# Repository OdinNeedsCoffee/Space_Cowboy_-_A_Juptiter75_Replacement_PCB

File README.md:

# Space_Cowboy_-_A_Juptiter75_Replacement_PCB

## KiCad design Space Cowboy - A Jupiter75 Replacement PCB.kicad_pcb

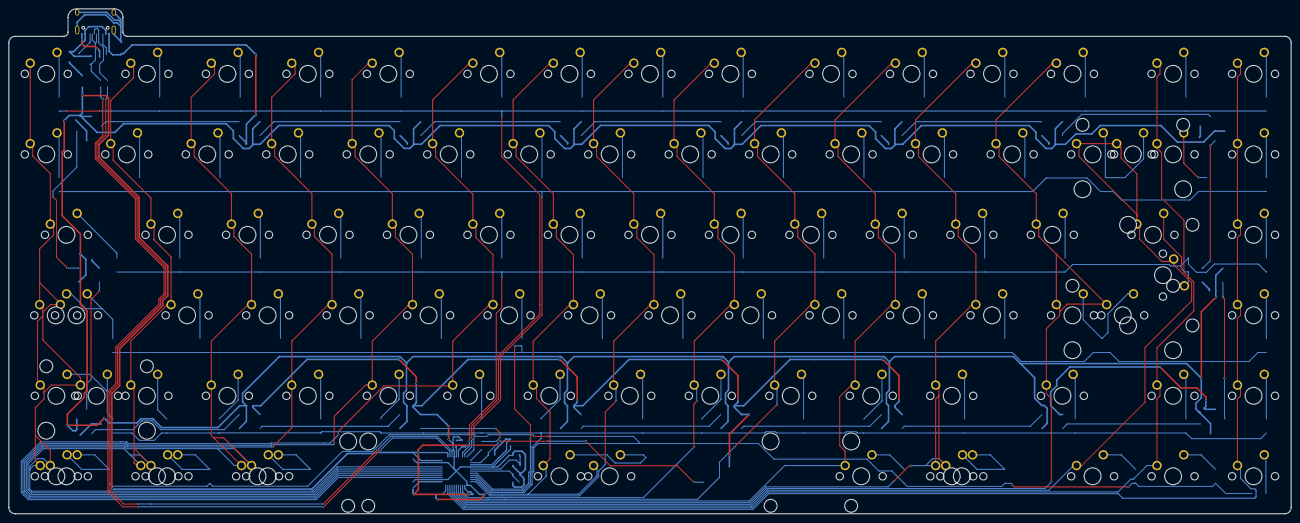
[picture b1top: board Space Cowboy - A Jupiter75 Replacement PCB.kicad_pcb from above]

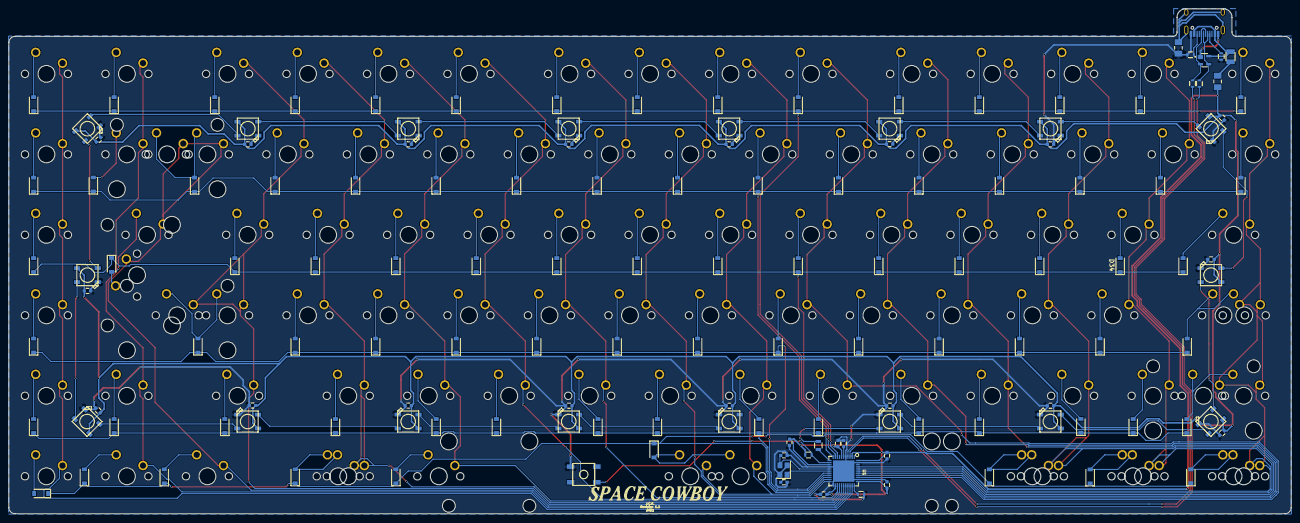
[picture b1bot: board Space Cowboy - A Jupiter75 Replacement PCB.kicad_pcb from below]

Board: 2 copper layers, 303.5 x 119.5 mm, 237 parts (143 on the bottom side), 124 nets.

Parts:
C1: 1uF; C_0603
C2, C3, C4, C8: 0.1uF; C_0603
C5: 10uF; C_0603
C6, C7: 22pF; C_0603
CRGB1, CRGB2, CRGB3, CRGB4, CRGB5, CRGB6, CRGB7, CRGB8, CRGB9, CRGB10, CRGB11, CRGB12, CRGB13, CRGB14, CRGB15, CRGB16, CRGB17, CRGB18: 0.1uF; C_0603
D1: PRTR5V0U2X; SOT190P230X110-4N
D2, D3, D4, D5, D6, D7, D8, D9, D10, D11, D12, D13, D14, D15, D16, D17, D18, D19, D20, D21, D22, D23, D24, D25, D26, D27, D28, D29, D30, D31, D32, D33, D34, D35, D36, D37, D38, D39, D40, D41, D42, D43, D44, D45, D46, D47, D48, D49, D50, D51, D52, D53, D54, D55, D56, D57, D58, D59, D60, D61, D62, D63, D64, D65, D66, D67, D68, D69, D70, D71, D72, D73, D74, D75, D76, D77, D78, D79, D80, D81, D82, D83, D84, D85: D_Small; D_SOD-123
DRGB1, DRGB2, DRGB3, DRGB4, DRGB5, DRGB6, DRGB7, DRGB8, DRGB9, DRGB10, DRGB11, DRGB12, DRGB13, DRGB14, DRGB15, DRGB16, DRGB17, DRGB18: WS2812B
F1: 500mA; Fuse_SMD1206_Reflow
FB1, FB2: 50Ohm@100MHz; BEADC3216X130N
MX_0, MX_1, MX_2, MX_3, MX_4, MX_5, MX_6, MX_7, MX_8, MX_9, MX_.1: MX-NoLED; MXOnly-1U
MX_#1: MX-NoLED; MXOnly-1U
MX_+1: MX-NoLED; MXOnly-1U
MX_,1: MX-NoLED; MXOnly-1U
MX_-1: MX-NoLED; MXOnly-1U
MX_A1: MX-NoLED; MXOnly-1U
MX_AE1: MX-NoLED; MXOnly-1U
MX_Alt1.5: MX-NoLED; MXOnly-1.5U
MX_Alt1.25: MX-NoLED; MXOnly-1.25U
MX_AltGr1.5: MX-NoLED; MXOnly-1.5U
MX_AltGr1.25: MX-NoLED; MXOnly-1.25U
MX_B1: MX-NoLED; MXOnly-1U
MX_Backspace2: MX-NoLED; MXOnly-2U
MX_C1: MX-NoLED; MXOnly-1U
MX_Caps1: MX-NoLED; MXOnly-1.75U
MX_CapsS1: MX-NoLED; MXOnly-1.75U
MX_Ctrl1.5: MX-NoLED; MXOnly-1.5U
MX_Ctrl1.25: MX-NoLED; MXOnly-1.25U
MX_D1: MX-NoLED; MXOnly-1U
MX_Delete1: MX-NoLED; MXOnly-1U
MX_Down1: MX-NoLED; MXOnly-1U
MX_E1: MX-NoLED; MXOnly-1U
MX_End1: MX-NoLED; MXOnly-1U
MX_EnterANSI2.25: MX-NoLED; MXOnly-2.25U
MX_EnterISO1: MX-NoLED; MXOnly-2U
MX_Esc1: MX-NoLED; MXOnly-1U
MX_F1, MX_F2, MX_F3, MX_F4, MX_F5, MX_F6, MX_F7, MX_F8, MX_F9, MX_F10, MX_F11, MX_F12, MX_F13: MX-NoLED; MXOnly-1U
MX_G1: MX-NoLED; MXOnly-1U
MX_H1: MX-NoLED; MXOnly-1U
MX_Home1: MX-NoLED; MXOnly-1U
MX_I1: MX-NoLED; MXOnly-1U
MX_Insert1: MX-NoLED; MXOnly-1U
MX_J1: MX-NoLED; MXOnly-1U
MX_K1: MX-NoLED; MXOnly-1U
MX_L1: MX-NoLED; MXOnly-1U
MX_LShift1: MX-NoLED; MXOnly-2.25U
MX_LShiftIso1: MX-NoLED; MXOnly-1.25U
MX_Left1: MX-NoLED; MXOnly-1U
MX_M1: MX-NoLED; MXOnly-1U
MX_N1: MX-NoLED; MXOnly-1U
MX_NebenSS1: MX-NoLED; MXOnly-1U
MX_O1: MX-NoLED; MXOnly-1U
MX_OE1: MX-NoLED; MXOnly-1U
MX_P1: MX-NoLED; MXOnly-1U
MX_PauseB1: MX-NoLED; MXOnly-1U
MX_PgUp1: MX-NoLED; MXOnly-1U
MX_Q1: MX-NoLED; MXOnly-1U
MX_R1: MX-NoLED; MXOnly-1U
MX_Right1: MX-NoLED; MXOnly-1U
MX_S1: MX-NoLED; MXOnly-1U
MX_SS1: MX-NoLED; MXOnly-1U
MX_ScrollL1: MX-NoLED; MXOnly-1U
MX_Shift1.75: MX-NoLED; MXOnly-1.75U
MX_Space6.25: MX-NoLED; MXOnlyNoLED-6.25U-ReversedStabilizers
MX_Space7: MX-NoLED; MXOnly-7U-ReversedStabilizers_NoLED
MX_T1: MX-NoLED; MXOnly-1U
MX_Tab1: MX-NoLED; MXOnly-1.5U
MX_Tilde1: MX-NoLED; MXOnly-1U
MX_Tilde1.5: MX-NoLED; MXOnly-1.5U
MX_TildeIso1: MX-NoLED; MXOnly-1U
MX_U1: MX-NoLED; MXOnly-1U
MX_UE1: MX-NoLED; MXOnly-1U
MX_UnterEsc1: MX-NoLED; MXOnly-1U
MX_Up1: MX-NoLED; MXOnly-1U
MX_V1: MX-NoLED; MXOnly-1U
MX_W1: MX-NoLED; MXOnly-1U
MX_Win1: MX-NoLED; MXOnly-1U
MX_Win1.25, MX_Win1.252: MX-NoLED; MXOnly-1.25U
MX_X1: MX-NoLED; MXOnly-1U
MX_Y1: MX-NoLED; MXOnly-1U
MX_Z1: MX-NoLED; MXOnly-1U
R1, R4: 10k; R_0603
R2, R3: 22; R_0603
R5, R6: 5.1k; R_0603
R7: 0.5k; R_0805
SW1: SW_PUSH; SKQG-1155865
U1: ATmega32U4-AU; QFN44G-0.5-7X7MM
USB1: HRO-TYPE-C-31-M-12
Y1: 16MHz; Crystal_SMD_3225-4pin_3.2x2.5mm

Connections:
+5V: C2.1, C3.1, C4.1, C5.2, C8.1, CRGB1.1, CRGB2.1, CRGB3.1, CRGB4.1, CRGB5.1, CRGB6.1, CRGB7.1, CRGB8.1, CRGB9.1, CRGB10.1, CRGB11.1, CRGB12.1, CRGB13.1, CRGB14.1, CRGB15.1, CRGB16.1, CRGB17.1, CRGB18.1, DRGB1.1VDD, DRGB2.1VDD, DRGB3.1VDD, DRGB4.1VDD, DRGB5.1VDD, DRGB6.1VDD, DRGB7.1VDD, DRGB8.1VDD, DRGB9.1VDD, DRGB10.1VDD, DRGB11.1VDD, DRGB12.1VDD, DRGB13.1VDD, DRGB14.1VDD, DRGB15.1VDD, DRGB16.1VDD, DRGB17.1VDD, DRGB18.1VDD, FB1.1, R4.2, U1.2, U1.7, U1.14, U1.24, U1.34, U1.44
COL0: MX_Caps1.1, MX_CapsS1.1, MX_Ctrl1.5.1, MX_Ctrl1.25.1, MX_Esc1.1, MX_LShift1.1, MX_LShiftIso1.1, MX_Tab1.1, MX_UnterEsc1.1, U1.41
COL1: MX_1.1, MX_A1.1, MX_F1.1, MX_Q1.1, MX_TildeIso1.1, MX_Win1.1, MX_Win1.25.1, U1.40
COL2: MX_2.1, MX_Alt1.5.1, MX_Alt1.25.1, MX_F2.1, MX_S1.1, MX_W1.1, MX_Y1.1, U1.39
COL3: MX_3.1, MX_D1.1, MX_E1.1, MX_F3.1, MX_X1.1, U1.38
COL4: MX_4.1, MX_C1.1, MX_F4.1, MX_F13.1, MX_R1.1, U1.37
COL5: MX_5.1, MX_F5.1, MX_G1.1, MX_T1.1, MX_V1.1, U1.36
COL6: MX_6.1, MX_B1.1, MX_F6.1, MX_H1.1, MX_Space6.25.1, MX_Space7.1, MX_Z1.1, U1.21
COL7: MX_7.1, MX_F7.1, MX_J1.1, MX_N1.1, MX_U1.1, U1.22
COL8: MX_8.1, MX_F8.1, MX_I1.1, MX_K1.1, MX_M1.1, U1.25
COL9: MX_9.1, MX_,1.1, MX_F9.1, MX_L1.1, MX_O1.1, U1.26
COL10: MX_0.1, MX_.1.1, MX_AltGr1.25.1, MX_F10.1, MX_OE1.1, MX_P1.1, U1.27
COL11: MX_-1.1, MX_AE1.1, MX_AltGr1.5.1, MX_F11.1, MX_SS1.1, MX_UE1.1, MX_Win1.252.1, U1.28
COL12: MX_#1.1, MX_+1.1, MX_EnterANSI2.25.1, MX_F12.1, MX_NebenSS1.1, MX_Shift1.75.1, U1.29
COL13: MX_Backspace2.1, MX_EnterISO1.1, MX_Left1.1, MX_Tilde1.1, MX_Tilde1.5.1, U1.30
COL14: MX_Delete1.1, MX_Down1.1, MX_ScrollL1.1, MX_Up1.1, U1.31
COL15: MX_End1.1, MX_Home1.1, MX_Insert1.1, MX_PauseB1.1, MX_PgUp1.1, MX_Right1.1, U1.32
D+: D1.2, R2.1, USB1.6, USB1.8
D-: D1.3, R3.2, USB1.5, USB1.7
GND: C1.1, C2.2, C3.2, C4.2, C5.1, C6.1, C7.2, C8.2, CRGB1.2, CRGB2.2, CRGB3.2, CRGB4.2, CRGB5.2, CRGB6.2, CRGB7.2, CRGB8.2, CRGB9.2, CRGB10.2, CRGB11.2, CRGB12.2, CRGB13.2, CRGB14.2, CRGB15.2, CRGB16.2, CRGB17.2, CRGB18.2, D1.1, DRGB1.3GND, DRGB2.3GND, DRGB3.3GND, DRGB4.3GND, DRGB5.3GND, DRGB6.3GND, DRGB7.3GND, DRGB8.3GND, DRGB9.3GND, DRGB10.3GND, DRGB11.3GND, DRGB12.3GND, DRGB13.3GND, DRGB14.3GND, DRGB15.3GND, DRGB16.3GND, DRGB17.3GND, DRGB18.3GND, FB2.1, R1.2, R5.2, R6.2, SW1.1, U1.5, U1.15, U1.23, U1.35, U1.43, U1.TAB, USB1.1, USB1.12, Y1.2, Y1.4
unnamed: C1.2, U1.6
unnamed: C6.2, U1.17, Y1.1
unnamed: C7.1, U1.16, Y1.3
unnamed: D2.2, MX_Esc1.2
unnamed: D3.2, MX_F1.2
unnamed: D4.2, MX_F2.2
unnamed: D5.2, MX_F3.2
unnamed: D6.2, MX_F4.2
unnamed: D7.2, MX_F5.2
unnamed: D8.2, MX_F6.2
unnamed: D9.2, MX_F7.2
unnamed: D10.2, MX_F8.2
unnamed: D11.2, MX_F9.2
unnamed: D12.2, MX_F10.2
unnamed: D13.2, MX_F11.2
unnamed: D14.2, MX_F12.2
unnamed: D15.2, MX_ScrollL1.2
unnamed: D16.2, MX_PauseB1.2
unnamed: D17.2, MX_UnterEsc1.2
unnamed: D18.2, MX_1.2
unnamed: D19.2, MX_2.2
unnamed: D20.2, MX_3.2
unnamed: D21.2, MX_4.2
unnamed: D22.2, MX_5.2
unnamed: D23.2, MX_6.2
unnamed: D24.2, MX_7.2
unnamed: D25.2, MX_8.2
unnamed: D26.2, MX_9.2
unnamed: D27.2, MX_0.2
unnamed: D28.2, MX_SS1.2
unnamed: D29.2, MX_NebenSS1.2
unnamed: D30.2, MX_Backspace2.2, MX_Tilde1.2
unnamed: D31.2, MX_Delete1.2
unnamed: D32.2, MX_Insert1.2
unnamed: D33.2, MX_Tab1.2
unnamed: D34.2, MX_Q1.2
unnamed: D35.2, MX_W1.2
unnamed: D36.2, MX_E1.2
unnamed: D37.2, MX_R1.2
unnamed: D38.2, MX_T1.2
unnamed: D39.2, MX_Z1.2
unnamed: D40.2, MX_U1.2
unnamed: D41.2, MX_I1.2
unnamed: D42.2, MX_O1.2
unnamed: D43.2, MX_P1.2
unnamed: D44.2, MX_UE1.2
unnamed: D45.2, MX_+1.2
unnamed: D46.2, MX_EnterISO1.2, MX_Tilde1.5.2
unnamed: D47.2, MX_PgUp1.2
unnamed: D48.2, MX_Caps1.2, MX_CapsS1.2
unnamed: D49.2, MX_A1.2
unnamed: D50.2, MX_S1.2
unnamed: D51.2, MX_D1.2
unnamed: D52.2, MX_F13.2
unnamed: D53.2, MX_G1.2
unnamed: D54.2, MX_H1.2
unnamed: D55.2, MX_J1.2
unnamed: D56.2, MX_K1.2
unnamed: D57.2, MX_L1.2
unnamed: D58.2, MX_OE1.2
unnamed: D59.2, MX_AE1.2
unnamed: D60.2, MX_#1.2, MX_EnterANSI2.25.2
unnamed: D61.2, MX_Home1.2
unnamed: D62.2, MX_LShift1.2, MX_LShiftIso1.2
unnamed: D63.2, MX_TildeIso1.2
unnamed: D64.2, MX_Y1.2
unnamed: D65.2, MX_X1.2
unnamed: D66.2, MX_C1.2
unnamed: D67.2, MX_V1.2
unnamed: D68.2, MX_B1.2
unnamed: D69.2, MX_N1.2
unnamed: D70.2, MX_M1.2
unnamed: D71.2, MX_,1.2
unnamed: D72.2, MX_.1.2
unnamed: D73.2, MX_-1.2
unnamed: D74.2, MX_Shift1.75.2
unnamed: D75.2, MX_Up1.2
unnamed: D76.2, MX_End1.2
unnamed: D77.2, MX_Ctrl1.5.2, MX_Ctrl1.25.2
unnamed: D78.2, MX_Win1.2, MX_Win1.25.2
unnamed: D79.2, MX_Alt1.5.2, MX_Alt1.25.2
unnamed: D80.2, MX_Space6.25.2, MX_Space7.2
unnamed: D81.2, MX_AltGr1.25.2
unnamed: D82.2, MX_AltGr1.5.2, MX_Win1.252.2
unnamed: D83.2, MX_Left1.2
unnamed: D84.2, MX_Down1.2
unnamed: D85.2, MX_Right1.2
unnamed: F1.2, FB1.2
unnamed: FB2.2, USB1.13
unnamed: R1.1, U1.33
unnamed: R2.2, U1.4
unnamed: R3.1, U1.3
unnamed: R4.1, SW1.2, U1.13
unnamed: R5.1, USB1.4
unnamed: R6.1, USB1.10
unnamed: R7.2, U1.12
RGB_DI_PIN: DRGB18.4DIN, R7.1
ROW0: D2.1, D3.1, D4.1, D5.1, D6.1, D7.1, D8.1, D9.1, D10.1, D11.1, D12.1, D13.1, D14.1, D15.1, D16.1, U1.10
ROW1: D17.1, D18.1, D19.1, D20.1, D21.1, D22.1, D23.1, D24.1, D25.1, D26.1, D27.1, D28.1, D29.1, D30.1, D31.1, D32.1, U1.11
ROW2: D33.1, D34.1, D35.1, D36.1, D37.1, D38.1, D39.1, D40.1, D41.1, D42.1, D43.1, D44.1, D45.1, D46.1, D47.1, U1.9
ROW3: D48.1, D49.1, D50.1, D51.1, D52.1, D53.1, D54.1, D55.1, D56.1, D57.1, D58.1, D59.1, D60.1, D61.1, U1.18
ROW4: D62.1, D63.1, D64.1, D65.1, D66.1, D67.1, D68.1, D69.1, D70.1, D71.1, D72.1, D73.1, D74.1, D75.1, D76.1, U1.19
ROW5: D77.1, D78.1, D79.1, D80.1, D81.1, D82.1, D83.1, D84.1, D85.1, U1.20
VBUS: D1.4, F1.1, USB1.2, USB1.11

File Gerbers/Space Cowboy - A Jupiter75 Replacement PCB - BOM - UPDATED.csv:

Comment,Designator,Footprint,LCSC Part Number
10k,R1,R_0603,C15401
10k,R4,R_0603,C15401
5.1k,R5,R_0603,C23186
5.1k,R6,R_0603,C23186
500mA,F1,Fuse_SMD1206_Reflow,C209741
PRTR5V0U2X,D1,PRTR5V0U2X:SOT190P230X110-4N,C12333
D_Small,D2,D_SOD-123,C81598
D_Small,D3,D_SOD-123,C81598
D_Small,D4,D_SOD-123,C81598
D_Small,D5,D_SOD-123,C81598
D_Small,D6,D_SOD-123,C81598
D_Small,D7,D_SOD-123,C81598
D_Small,D8,D_SOD-123,C81598
D_Small,D9,D_SOD-123,C81598
D_Small,D10,D_SOD-123,C81598
D_Small,D11,D_SOD-123,C81598
D_Small,D12,D_SOD-123,C81598
D_Small,D13,D_SOD-123,C81598
D_Small,D14,D_SOD-123,C81598
D_Small,D15,D_SOD-123,C81598
D_Small,D16,D_SOD-123,C81598
D_Small,D17,D_SOD-123,C81598
D_Small,D18,D_SOD-123,C81598
D_Small,D19,D_SOD-123,C81598
D_Small,D20,D_SOD-123,C81598
D_Small,D21,D_SOD-123,C81598
D_Small,D22,D_SOD-123,C81598
D_Small,D23,D_SOD-123,C81598
D_Small,D24,D_SOD-123,C81598
D_Small,D25,D_SOD-123,C81598
D_Small,D26,D_SOD-123,C81598
D_Small,D27,D_SOD-123,C81598
D_Small,D28,D_SOD-123,C81598
D_Small,D29,D_SOD-123,C81598
D_Small,D30,D_SOD-123,C81598
D_Small,D31,D_SOD-123,C81598
D_Small,D32,D_SOD-123,C81598
D_Small,D33,D_SOD-123,C81598
D_Small,D34,D_SOD-123,C81598
D_Small,D35,D_SOD-123,C81598
D_Small,D36,D_SOD-123,C81598
D_Small,D37,D_SOD-123,C81598
D_Small,D38,D_SOD-123,C81598
D_Small,D39,D_SOD-123,C81598
D_Small,D40,D_SOD-123,C81598
D_Small,D41,D_SOD-123,C81598
D_Small,D42,D_SOD-123,C81598
D_Small,D43,D_SOD-123,C81598
D_Small,D44,D_SOD-123,C81598
D_Small,D45,D_SOD-123,C81598
D_Small,D46,D_SOD-123,C81598
D_Small,D47,D_SOD-123,C81598
D_Small,D48,D_SOD-123,C81598
D_Small,D49,D_SOD-123,C81598
D_Small,D50,D_SOD-123,C81598
D_Small,D51,D_SOD-123,C81598
D_Small,D52,D_SOD-123,C81598
D_Small,D53,D_SOD-123,C81598
D_Small,D54,D_SOD-123,C81598
D_Small,D55,D_SOD-123,C81598
D_Small,D56,D_SOD-123,C81598
D_Small,D57,D_SOD-123,C81598
D_Small,D58,D_SOD-123,C81598
D_Small,D59,D_SOD-123,C81598
D_Small,D60,D_SOD-123,C81598
D_Small,D61,D_SOD-123,C81598
D_Small,D62,D_SOD-123,C81598
D_Small,D63,D_SOD-123,C81598
D_Small,D64,D_SOD-123,C81598
D_Small,D65,D_SOD-123,C81598
D_Small,D66,D_SOD-123,C81598
D_Small,D67,D_SOD-123,C81598
D_Small,D68,D_SOD-123,C81598
D_Small,D69,D_SOD-123,C81598
D_Small,D70,D_SOD-123,C81598
D_Small,D71,D_SOD-123,C81598
D_Small,D72,D_SOD-123,C81598
D_Small,D73,D_SOD-123,C81598
D_Small,D74,D_SOD-123,C81598
D_Small,D75,D_SOD-123,C81598
D_Small,D76,D_SOD-123,C81598
D_Small,D77,D_SOD-123,C81598
D_Small,D78,D_SOD-123,C81598
D_Small,D79,D_SOD-123,C81598
D_Small,D80,D_SOD-123,C81598
D_Small,D81,D_SOD-123,C81598
D_Small,D82,D_SOD-123,C81598
D_Small,D83,D_SOD-123,C81598
D_Small,D84,D_SOD-123,C81598
D_Small,D85,D_SOD-123,C81598
SW_PUSH,SW1,SKQG-1155865,C221856
16MHz,Y1,Crystal_SMD_3225-4pin_3.2x2.5mm,C13738
ATmega32U4-MUR,U1,ATmega32U4-MUR_QFN44:QFN44G-0.5-7X7MM,C45874
1uF,C1,C_0603,C29936
0.1uF,C2,C_0603,C24452
0.1uF,C3,C_0603,C24452
0.1uF,C4,C_0603,C24452
10uF,C5,C_0603,C96446
22pF,C6,C_0603,C1653
22pF,C7,C_0603,C1653
0.1uF,C8,C_0603,C24452
WS2812B,DRGB1,WS2812B Worldsemi:WS2812B,C114586
WS2812B,DRGB2,WS2812B Worldsemi:WS2812B,C114586
WS2812B,DRGB3,WS2812B Worldsemi:WS2812B,C114586
WS2812B,DRGB4,WS2812B Worldsemi:WS2812B,C114586
WS2812B,DRGB5,WS2812B Worldsemi:WS2812B,C114586
WS2812B,DRGB6,WS2812B Worldsemi:WS2812B,C114586
WS2812B,DRGB7,WS2812B Worldsemi:WS2812B,C114586
WS2812B,DRGB8,WS2812B Worldsemi:WS2812B,C114586
WS2812B,DRGB9,WS2812B Worldsemi:WS2812B,C114586
WS2812B,DRGB10,WS2812B Worldsemi:WS2812B,C114586
WS2812B,DRGB11,WS2812B Worldsemi:WS2812B,C114586
WS2812B,DRGB12,WS2812B Worldsemi:WS2812B,C114586
WS2812B,DRGB13,WS2812B Worldsemi:WS2812B,C114586
WS2812B,DRGB14,WS2812B Worldsemi:WS2812B,C114586
WS2812B,DRGB15,WS2812B Worldsemi:WS2812B,C114586
WS2812B,DRGB16,WS2812B Worldsemi:WS2812B,C114586
WS2812B,DRGB17,WS2812B Worldsemi:WS2812B,C114586
WS2812B,DRGB18,WS2812B Worldsemi:WS2812B,C114586
0.1uF,CRGB1,C_0603,C24452
0.1uF,CRGB2,C_0603,C24452
0.1uF,CRGB3,C_0603,C24452
0.1uF,CRGB4,C_0603,C24452
0.1uF,CRGB5,C_0603,C24452
0.1uF,CRGB6,C_0603,C24452
0.1uF,CRGB7,C_0603,C24452
0.1uF,CRGB8,C_0603,C24452
0.1uF,CRGB9,C_0603,C24452
0.1uF,CRGB10,C_0603,C24452
0.1uF,CRGB11,C_0603,C24452
0.1uF,CRGB12,C_0603,C24452
0.1uF,CRGB13,C_0603,C24452
0.1uF,CRGB14,C_0603,C24452
0.1uF,CRGB15,C_0603,C24452
0.1uF,CRGB16,C_0603,C24452
0.1uF,CRGB17,C_0603,C24452
0.1uF,CRGB18,C_0603,C24452
22,R2,R_0603,C23345
22,R3,R_0603,C23345

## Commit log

2020-12-23 Initialize Project
2020-12-23 Create fp-info-cache
2020-12-24 Create sym-lib-table
2020-12-24 Create Space Cowboy - A Jupiter75 Replacement PCB.sch-bak
2020-12-25 Create Space Cowboy RBG.sch-bak
2020-12-25 Update Space Cowboy - A Jupiter75 Replacement PCB.sch-bak
2020-12-27 Update Space Cowboy RBG.sch-bak
2020-12-27 Update fp-info-cache
2020-12-27 Create Space Cowboy - A Jupiter75 Replacement PCB.kicad_pcb-bak
2020-12-28 Update Space Cowboy - A Jupiter75 Replacement PCB.kicad_pcb-bak
